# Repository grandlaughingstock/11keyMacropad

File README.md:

This Macropad is a 11 key macropad with a rotary encoder, and uses QMK firmware

A screenshot of your overall hackpad

A screenshot of your schematic

A screenshot of your PCB

A screenshot of your case and how it'll fit together

1 unsoldered Seeed XIAO RP2040

9 x through-hole 1N4148 Diodes

11 x MX-Style switches

1 x EC11 Rotary Encoder

11 x white blank DSA keycaps

1 x Case

1 x PCB

4x M3x16mm screws

4x M3x5mx4mm heatset inserts

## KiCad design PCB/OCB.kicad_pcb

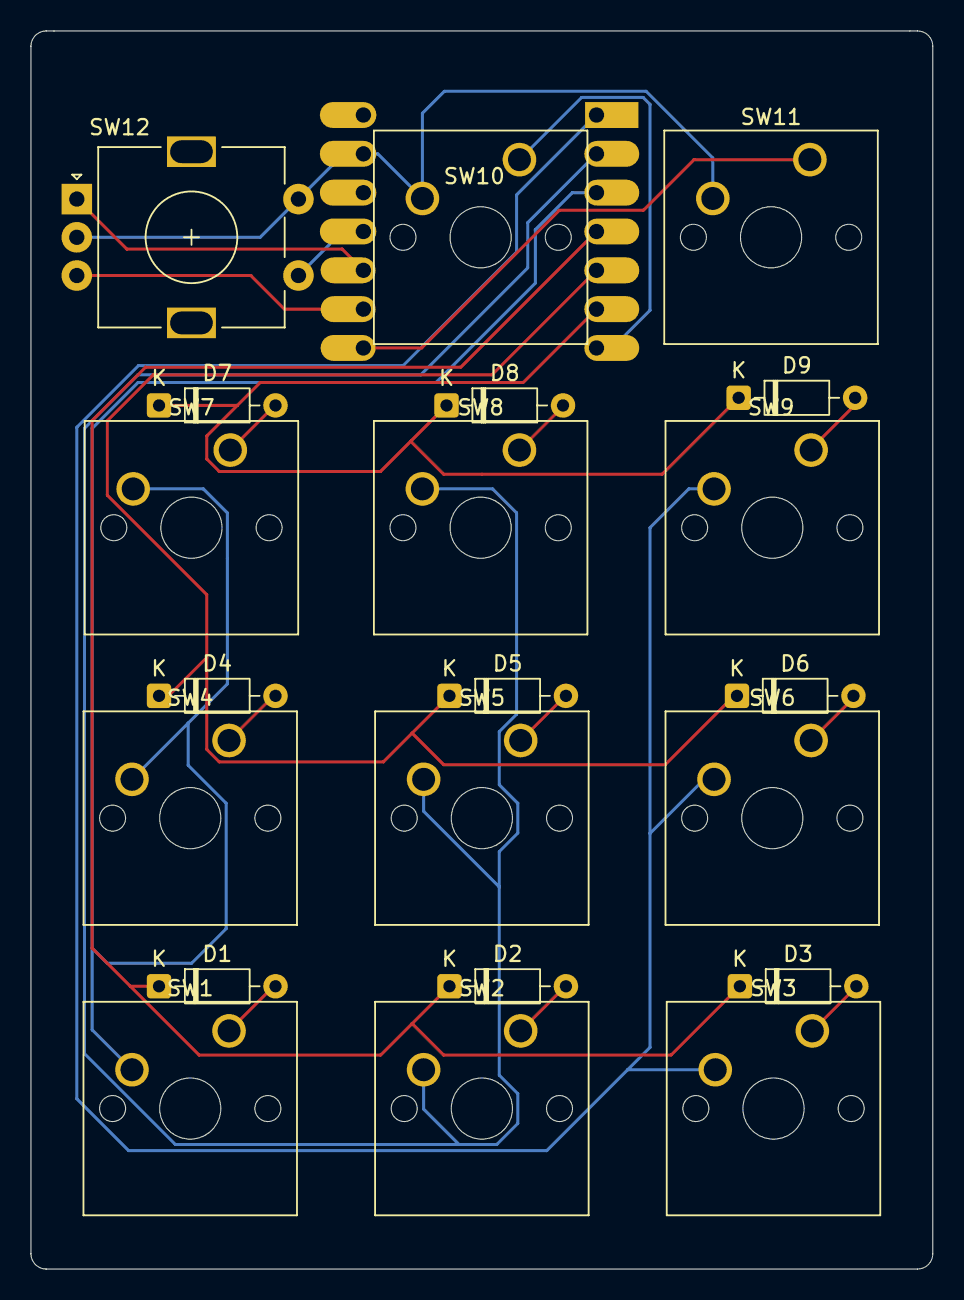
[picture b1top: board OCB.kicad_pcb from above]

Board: 2 copper layers, 59.0 x 81.0 mm, 22 parts (1 on the bottom side), 21 nets.

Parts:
D1, D2, D3, D4, D5, D6, D7, D8, D9: 1N4148; D_DO-35_SOD27_P7.62mm_Horizontal
SW1, SW2, SW3, SW4, SW5, SW6, SW7, SW8, SW9, SW10, SW11: SW_Push; SW_Cherry_MX_1.00u_PCB
SW12: RotaryEncoder_Switch; RotaryEncoder_Alps_EC11E-Switch_Vertical_H20mm
U4: MOUDLE-SEEEDUINO-XIAO; XIAO-Generic-Hybrid-14P-2.54-21X17.8MM

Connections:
GND: SW10.2, SW11.2, SW12.C, SW12.S2, U4.13 (GND)
unnamed: D1.2 (A), SW1.1
unnamed: D1.1 (K), D2.1 (K), D3.1 (K), U4.4 (PA11_A3_D3)
unnamed: D2.2 (A), SW2.1
unnamed: D3.2 (A), SW3.1
unnamed: D4.2 (A), SW4.1
unnamed: D4.1 (K), D5.1 (K), D6.1 (K), U4.5 (PA8_A4_D4_SDA)
unnamed: D5.2 (A), SW5.1
unnamed: D6.2 (A), SW6.1
unnamed: D7.2 (A), SW7.1
unnamed: D7.1 (K), D8.1 (K), D9.1 (K), U4.6 (PA9_A5_D5_SCL)
unnamed: D8.2 (A), SW8.1
unnamed: D9.2 (A), SW9.1
unnamed: SW3.2, SW6.2, SW9.2, U4.1 (PA02_A0_D0)
unnamed: SW2.2, SW5.2, SW8.2, U4.2 (PA4_A1_D1)
unnamed: SW12.A, U4.10 (PA5_A9_D9_MISO)
unnamed: SW12.S1, U4.11 (PA6_A10_D10_MOSI)
unnamed: SW12.B, U4.9 (PA7_A8_D8_SCK)
unnamed: SW1.2, SW4.2, SW7.2, U4.3 (PA10_A2_D2)
unnamed: SW10.1, U4.7 (PB08_A6_D6_TX)
unnamed: SW11.1, U4.8 (PB09_A7_D7_RX)

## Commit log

2026-03-22 Update README with images and descriptions
    Added images for overall hackpad, schematic, PCB, and case.
